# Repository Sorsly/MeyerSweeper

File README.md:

# MeyerSweeper
362 Mini Project - A minesweeper game realized with the 9S12C32
Alan Han, Thao Nguyen, Zhihao Lin

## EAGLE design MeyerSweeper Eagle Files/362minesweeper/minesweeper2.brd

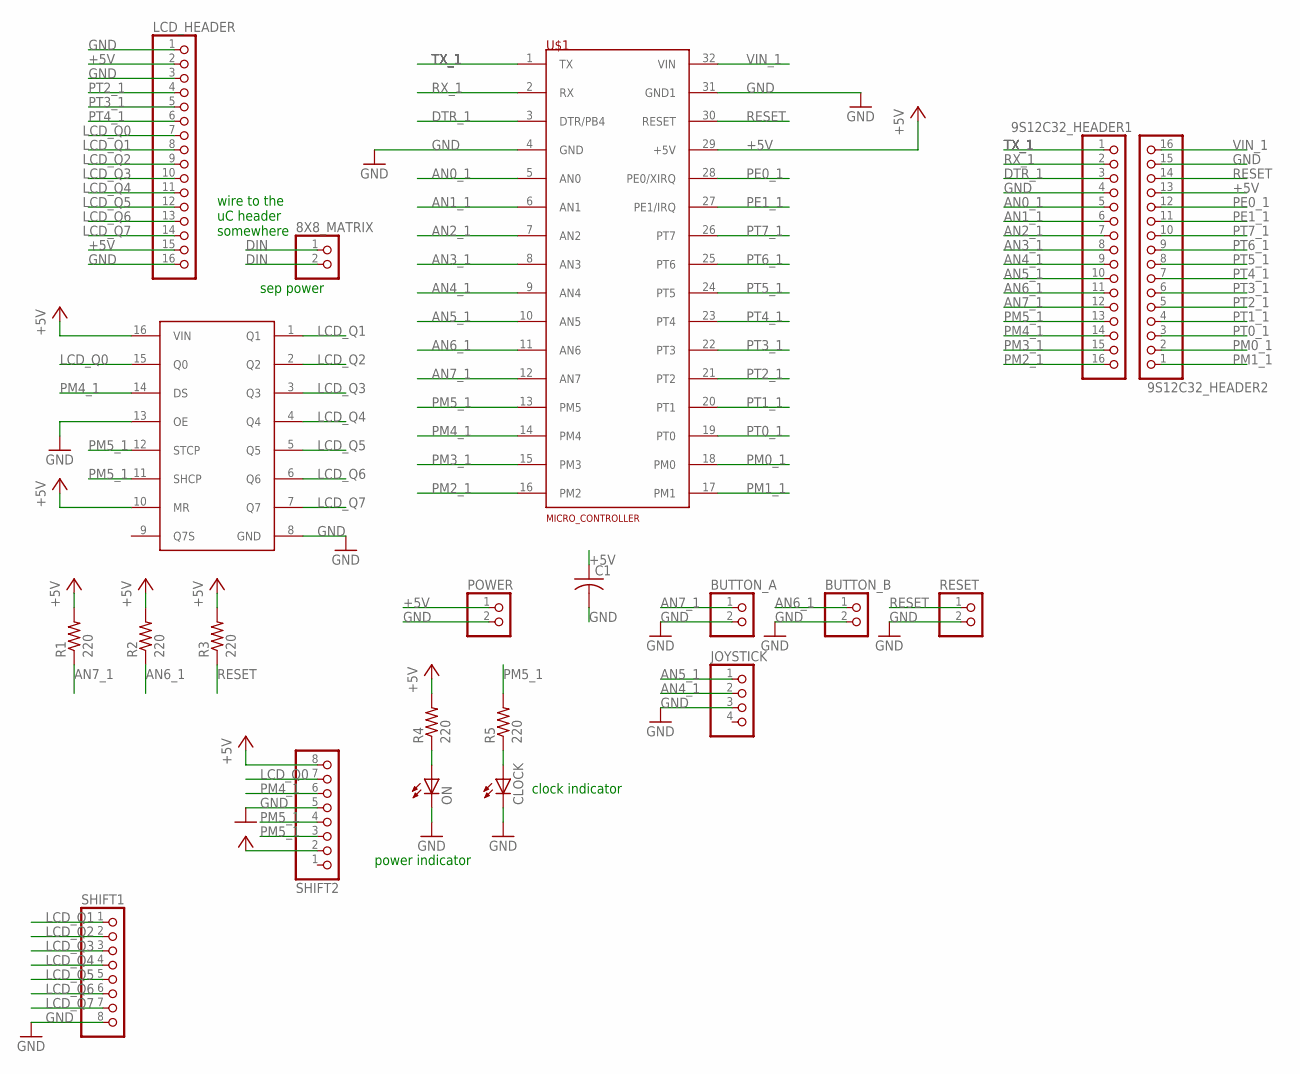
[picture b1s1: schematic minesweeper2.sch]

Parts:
8X8_MATRIX: PINHD-1X2; 1X02
9S12C32_HEADER1, 9S12C32_HEADER2: PINHD-1X16; 1X16
BUTTON_A: PINHD-1X2; 1X02
BUTTON_B: PINHD-1X2; 1X02
C1: C-US050-025X075; C050-025X075
CLOCK: LED5MM
JOYSTICK: PINHD-1X4; 1X04
LCD_HEADER: PINHD-1X16; 1X16
ON: LED5MM
POWER: PINHD-1X2; 1X02
R1, R2, R3, R4, R5: 220; 0207/10
RESET: PINHD-1X2; 1X02
SHIFT1, SHIFT2: PINHD-1X8; 1X08
U$1: MICRO_CONTROLLER
U$3: SHIFT_REGISTER; N5

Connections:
+5V: 9S12C32_HEADER2.13, C1.1, LCD_HEADER.2, LCD_HEADER.15, POWER.1, R1.2, R2.2, R3.2, R4.2, SHIFT2.2, SHIFT2.8, U$1.29 (+5V), U$3.10 (MR), U$3.16 (VIN)
AN0_1: 9S12C32_HEADER1.5, U$1.5 (AN0)
AN1_1: 9S12C32_HEADER1.6, U$1.6 (AN1)
AN2_1: 9S12C32_HEADER1.7, U$1.7 (AN2)
AN3_1: 9S12C32_HEADER1.8, U$1.8 (AN3)
AN4_1: 9S12C32_HEADER1.9, JOYSTICK.2, U$1.9 (AN4)
AN5_1: 9S12C32_HEADER1.10, JOYSTICK.1, U$1.10 (AN5)
AN6_1: 9S12C32_HEADER1.11, BUTTON_B.1, R2.1, U$1.11 (AN6)
AN7_1: 9S12C32_HEADER1.12, BUTTON_A.1, R1.1, U$1.12 (AN7)
DIN: 8X8_MATRIX.1, 8X8_MATRIX.2
DTR_1: 9S12C32_HEADER1.3, U$1.3 (DTR/PB4)
GND: 9S12C32_HEADER1.4, 9S12C32_HEADER2.15, BUTTON_A.2, BUTTON_B.2, C1.2, CLOCK.K (C), JOYSTICK.3, LCD_HEADER.1, LCD_HEADER.3, LCD_HEADER.16, ON.K (C), POWER.2, RESET.2, SHIFT1.8, SHIFT2.5, U$1.4 (GND), U$1.31 (GND1), U$3.8 (GND), U$3.13 (OE)
LCD_Q0: LCD_HEADER.7, SHIFT2.7, U$3.15 (Q0)
LCD_Q1: LCD_HEADER.8, SHIFT1.1, U$3.1 (Q1)
LCD_Q2: LCD_HEADER.9, SHIFT1.2, U$3.2 (Q2)
LCD_Q3: LCD_HEADER.10, SHIFT1.3, U$3.3 (Q3)
LCD_Q4: LCD_HEADER.11, SHIFT1.4, U$3.4 (Q4)
LCD_Q5: LCD_HEADER.12, SHIFT1.5, U$3.5 (Q5)
LCD_Q6: LCD_HEADER.13, SHIFT1.6, U$3.6 (Q6)
LCD_Q7: LCD_HEADER.14, SHIFT1.7, U$3.7 (Q7)
unnamed: ON.A, R4.1
unnamed: CLOCK.A, R5.1
PE0_1: 9S12C32_HEADER2.12, U$1.28 (PE0/XIRQ)
PE1_1: 9S12C32_HEADER2.11, U$1.27 (PE1/IRQ)
PM0_1: 9S12C32_HEADER2.2, U$1.18 (PM0)
PM1_1: 9S12C32_HEADER2.1, U$1.17 (PM1)
PM2_1: 9S12C32_HEADER1.16, U$1.16 (PM2)
PM3_1: 9S12C32_HEADER1.15, U$1.15 (PM3)
PM4_1: 9S12C32_HEADER1.14, SHIFT2.6, U$1.14 (PM4), U$3.14 (DS)
PM5_1: 9S12C32_HEADER1.13, R5.2, SHIFT2.3, SHIFT2.4, U$1.13 (PM5), U$3.11 (SHCP), U$3.12 (STCP)
PT0_1: 9S12C32_HEADER2.3, U$1.19 (PT0)
PT1_1: 9S12C32_HEADER2.4, U$1.20 (PT1)
PT2_1: 9S12C32_HEADER2.5, LCD_HEADER.4, U$1.21 (PT2)
PT3_1: 9S12C32_HEADER2.6, LCD_HEADER.5, U$1.22 (PT3)
PT4_1: 9S12C32_HEADER2.7, LCD_HEADER.6, U$1.23 (PT4)
PT5_1: 9S12C32_HEADER2.8, U$1.24 (PT5)
PT6_1: 9S12C32_HEADER2.9, U$1.25 (PT6)
PT7_1: 9S12C32_HEADER2.10, U$1.26 (PT7)
RESET: 9S12C32_HEADER2.14, R3.1, RESET.1, U$1.30 (RESET)
RX_1: 9S12C32_HEADER1.2, U$1.2 (RX)
TX_1: 9S12C32_HEADER1.1, U$1.1 (TX)
VIN_1: 9S12C32_HEADER2.16, U$1.32 (VIN)

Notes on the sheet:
wire to the uC header somewhere
power indicator
clock indicator
sep power

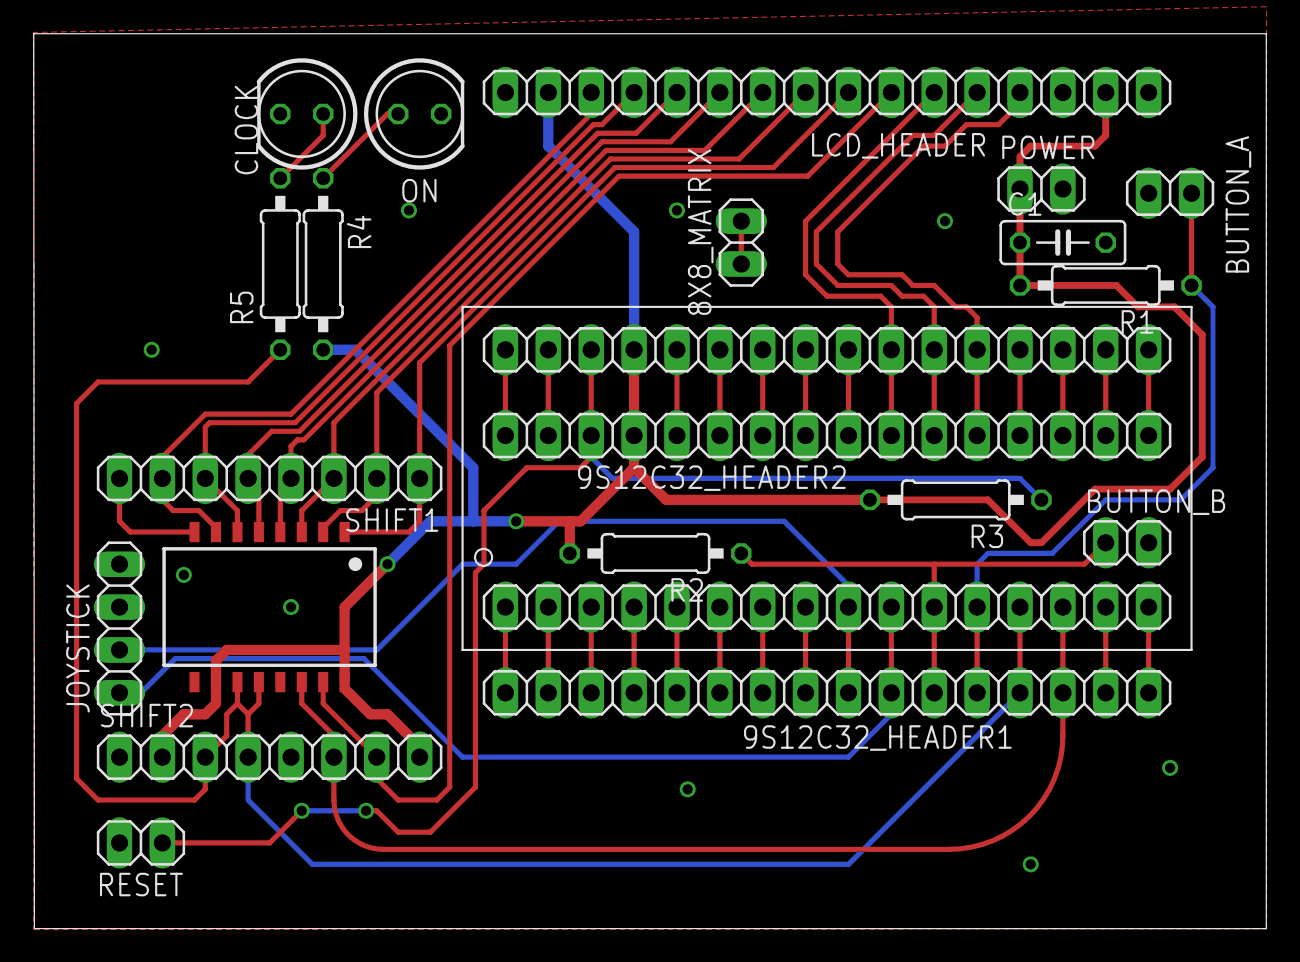
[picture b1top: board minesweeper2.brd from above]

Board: 2 copper layers, 73.0 x 53.0 mm, 21 parts (0 on the bottom side), 42 nets.

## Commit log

2016-04-18 README.md
2016-04-18 Added files via upload
2016-04-18 Changelog.md
2016-04-22 Reorganization
2016-04-22 moved README back to proper place
2016-04-25 tried to put Zhihao's raw game code into codewarrior
    -ran into 2 compile errors, check text doc for details
    -added obsolete code meant for ST7735; has some function changes
    (lcdwait is 1ms and flexible)
2016-04-26 codewarrior implementation fixes
    -swapped from time.h library functions to TIM interrupt functionality
    -commented out printf() statements
    -removed stdio.h and stdlib.h
    -renamed display enable vars to display1_en, display2_en
    -moved running game code to for loop section of main
2016-04-30 all code versions uploaded
